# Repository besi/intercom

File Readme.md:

# Intercom

A simple intercom based on [this blogpost](https://www.bastelnmitelektronik.de/basteleien-geräte-und-schaltungen/weitere-schaltungen-geräte-und-basteleien/sprechanlage/)

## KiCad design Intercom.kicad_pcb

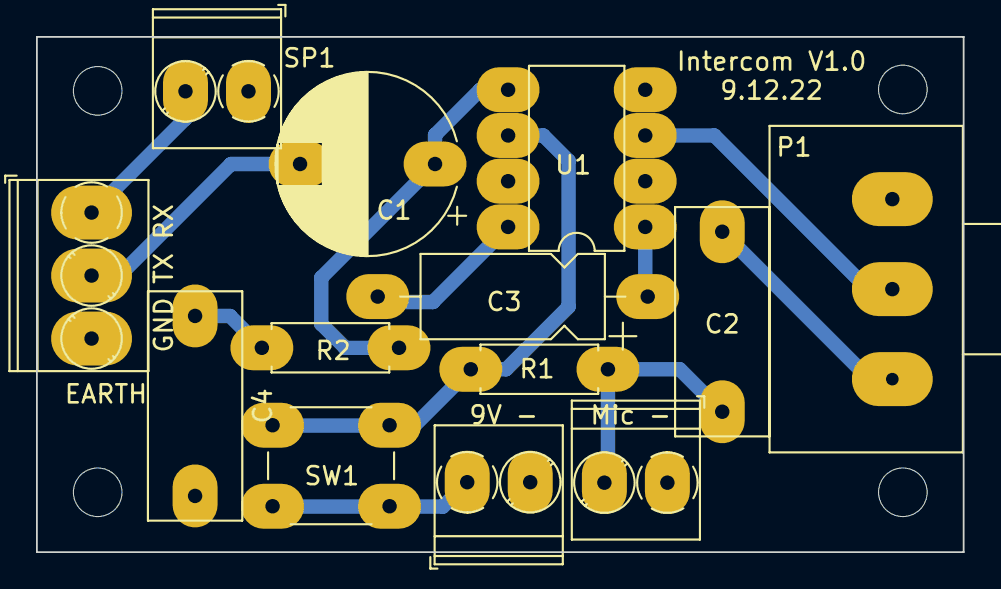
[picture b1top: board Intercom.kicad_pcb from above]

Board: 2 copper layers, 51.5 x 28.6 mm, 17 parts (0 on the bottom side), 12 nets.

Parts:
9V -: 9V; TerminalBlock_Phoenix_PT-1,5-2-3.5-H_1x02_P3.50mm_Horizontal
C1: 200u; CP_Radial_D10.0mm_P7.50mm
C2, C4: 100n; C_Disc_D12.5mm_W5.0mm_P10.00mm
C3: 10u; CP_Axial_L10.0mm_D4.5mm_P15.00mm_Horizontal
GND TX RX: To other; TerminalBlock_Phoenix_PT-1,5-3-3.5-H_1x03_P3.50mm_Horizontal
H1, H2, H3, H4: MountingHole; MountingHole_2.7mm_M2.5
Mic -: Microphone; TerminalBlock_Phoenix_PT-1,5-2-3.5-H_1x02_P3.50mm_Horizontal
P1: 22k; Potentiometer_Alps_RK163_Single_Horizontal
R1: 10k; R_Axial_DIN0207_L6.3mm_D2.5mm_P7.62mm_Horizontal
R2: 100; R_Axial_DIN0207_L6.3mm_D2.5mm_P7.62mm_Horizontal
SP1: Speaker; TerminalBlock_Phoenix_PT-1,5-2-3.5-H_1x02_P3.50mm_Horizontal
SW1: SW_Push; SW_PUSH_6mm_H4.3mm
U1: LM386; DIP-8_W7.62mm

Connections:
Earth: 9V -.2 (-), C4.2, GND TX RX.3, Mic -.1 (-), P1.3, SP1.1, U1.2 (-), U1.4 (GND)
unnamed: 9V -.1 (+), SW1.1
unnamed: C1.1, R2.2, U1.5
unnamed: C1.2, GND TX RX.2
unnamed: C2.1, P1.1
unnamed: C2.2, Mic -.2 (+), R1.2
unnamed: C3.1, U1.1 (GAIN)
unnamed: C3.2, U1.8 (GAIN)
unnamed: C4.1, R2.1
unnamed: GND TX RX.1, SP1.2
unnamed: P1.2, U1.3 (+)
unnamed: R1.1, SW1.2, U1.6 (V+)

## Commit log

2022-12-08 Created schematic and first version of PCB
2022-12-08 Add documentatoin
2022-12-08 More compact layout
2022-12-09 Prepare for milling v1.0
2022-12-09 Rename to Intercom
2022-12-09 Update drill file
